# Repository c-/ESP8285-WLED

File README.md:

This is a WLED board built around an ESP-8285, designed to be milled on
a CNC.

Parts include the ESP8285, a PCB trace antenna, an optional external
antenna connector, CH340K USB controller (with support for ESP
auto-programming), TXS0101 level shifter, an ME3115
buck converter (for WS2811 projects), and a ME6211 3.3V LDO. This stuff
is, for the most part, straight out of the data sheets so there shouldn't
be anything too exciting.

There's no real attempt to do any antenna tuning, impedance matching, etc.
I used the D1 mini pro as a guideline and basically cross my fingers.

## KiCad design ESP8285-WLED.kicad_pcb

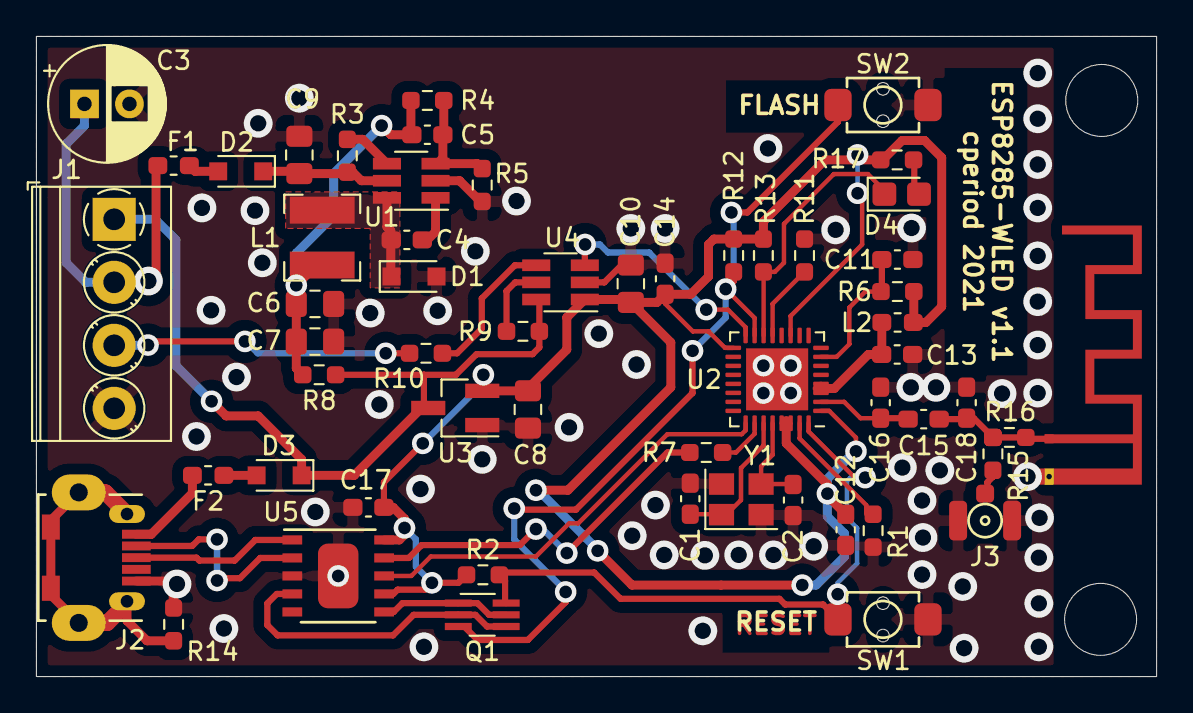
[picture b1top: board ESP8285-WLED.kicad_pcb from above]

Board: 2 copper layers, 62.2 x 35.6 mm, 58 parts (0 on the bottom side), 39 nets.

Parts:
AE1: PCB_ANTENNA; Texas_SWRA117D_2.4GHz_Left
C1, C2: 10p; C_0603_1608Metric_Pad1.08x0.95mm_HandSolder
C3: 220u; CP_Radial_D6.3mm_P2.50mm
C4: 220n; C_0603_1608Metric_Pad1.08x0.95mm_HandSolder
C5: 100p; C_0603_1608Metric_Pad1.08x0.95mm_HandSolder
C6, C7, C8: 22u; C_0805_2012Metric_Pad1.18x1.45mm_HandSolder
C9: 22u 25v; C_0805_2012Metric_Pad1.18x1.45mm_HandSolder
C10: 10u; C_0805_2012Metric_Pad1.18x1.45mm_HandSolder
C11, C12, C17: 100n; C_0603_1608Metric_Pad1.08x0.95mm_HandSolder
C13: TBD; C_0603_1608Metric_Pad1.08x0.95mm_HandSolder
C14: 1u; C_0603_1608Metric_Pad1.08x0.95mm_HandSolder
C15: 5.6p; C_0603_1608Metric_Pad1.08x0.95mm_HandSolder
C16, C18: DNP; C_0603_1608Metric_Pad1.08x0.95mm_HandSolder
D1, D2, D3: B5817W; D_SOD-323_HandSoldering
D4: LED; LED_0805_2012Metric_Castellated
F1, F2: 500mA; Fuse_0603_1608Metric_Pad1.05x0.95mm_HandSolder
H1, H2: MountingHole; MountingHole_4mm
J1: WLED; TerminalBlock_Phoenix_PT-1,5-4-3.5-H_1x04_P3.50mm_Horizontal
J2: USB_B_Micro; USB_Micro-B_CNC_C10418
J3: ANT; IPX_Connector_C496552
L1: 10uH 1A; L_Bourns-SRN4018
L2: 4.3nH; L_0603_1608Metric_Pad1.05x0.95mm_HandSolder
Q1: UMH3N; SOT-363_SC-70-6_Handsoldering
R1: 12K 1%; R_0603_1608Metric_Pad0.98x0.95mm_HandSolder
R2, R6, R11, R12, R13: 12K; R_0603_1608Metric_Pad0.98x0.95mm_HandSolder
R3: 1M; R_0603_1608Metric_Pad0.98x0.95mm_HandSolder
R4: 56K; R_0603_1608Metric_Pad0.98x0.95mm_HandSolder
R5, R9: 10K; R_0603_1608Metric_Pad0.98x0.95mm_HandSolder
R7: 499R; R_0603_1608Metric_Pad0.98x0.95mm_HandSolder
R8, R14, R16: 0R; R_0603_1608Metric_Pad0.98x0.95mm_HandSolder
R10: 470R; R_0603_1608Metric_Pad0.98x0.95mm_HandSolder
R15: DNP; R_0603_1608Metric_Pad0.98x0.95mm_HandSolder
R17: 1K; R_0603_1608Metric_Pad0.98x0.95mm_HandSolder
SW1: RESET; SW_Tact_C354947
SW2: FLASH; SW_Tact_C354947
U1: ME3116; SOT-23-6_Handsoldering
U2: ESP8285; QFN-32-1EP_5x5mm_P0.5mm_EP3.45x3.45mm
U3: ME6211; SOT-23_Handsoldering
U4: TXS0101; SOT-23-6_Handsoldering
U5: CH340K; eSSOP-10_3.9x4.9mm_P1.00mm
Y1: 26MHz; Crystal_SMD_3225-4Pin_3.2x2.5mm

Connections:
+3V3: C8.2, C10.2, C12.2, C14.2, C17.1, L2.1, R2.2, R6.2, R12.2, R13.2, R17.2, U2.1, U2.11, U2.17, U2.29, U2.30, U3.2, U4.1, U5.7, U5.10
+5V: D3.1, J1.1, R8.1, R9.1, U3.3, U4.6
+12V: C3.1, F1.1, J1.2
/5VOUT: C5.1, C6.1, C7.1, L1.2, R4.1, R8.2
/12VIN: C9.1, D2.1, R3.1, U1.5
/ANT_LNA: C15.2, C16.2, U2.2
/BEN: R3.2, U1.4
/BS: C4.2, U1.1
/CUTXD: R7.1, U5.9
/D+: J2.3, U5.1
/D-: J2.2, U5.2
/DTR: Q1.2, Q1.4, U5.4
/EN: C11.2, R6.1, U2.7
/FB: C5.2, R4.2, R5.1, U1.3
/GPIO0: Q1.3, R12.1, SW2.1, U2.15
/GPIO2: D4.1, R13.1, U2.14
/GPIO15: R11.2, U2.13
/RES12K: R1.1, U2.31
/RST: Q1.6, R2.1, SW1.1, U2.32
/RTS: Q1.1, Q1.5, U5.6
/SW: C4.1, D1.1, L1.1, U1.6
/URXD: U2.25, U5.8
/UTXD: R7.2, U2.26
/XI: C2.1, U2.28, Y1.3
/XO: C1.2, U2.27, Y1.1
GND: AE1.2, C1.1, C2.2, C3.2, C6.2, C7.2, C8.1, C9.2, C10.1, C11.1, C12.1, C13.1, C14.1, C16.1, C17.2, C18.1, D1.2, J1.4, J2.5, J3.2, R1.2, R5.2, R11.1, R14.1, SW1.2, SW2.2, U1.2, U2.33, U3.1, U4.2, U5.0, U5.3, Y1.2, Y1.4
unnamed: AE1.1, R16.2
unnamed: C13.2, L2.2, U2.3, U2.4
unnamed: C15.1, C18.2, R15.2, R16.1
unnamed: D2.2, F1.2
unnamed: D3.2, F2.1
unnamed: D4.2, R17.1
unnamed: F2.2, J2.1
unnamed: J1.3, R10.1
unnamed: J2.6, R14.2
unnamed: J3.1, R15.1
unnamed: R9.2, U4.5
unnamed: R10.2, U4.4
WLED: U2.16, U4.3

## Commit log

2021-07-02 added Makefile
2021-07-02 added antenna track width
2021-07-02 tweaking and cleanups
2021-07-02 more tidying
2021-07-02 adjustments around the crystal
2021-07-02 more tweaking
2021-07-03 more adjustments
2021-07-03 even more tweaks
2021-07-09 updates and tweaks based on actually building one
2021-07-09 add a schematic pdf, minor doc tweaks
2021-07-09 add a picture
2021-07-09 documentation
2021-07-09 fix image
2021-07-09 fix it again
2021-07-09 warning about antenna
